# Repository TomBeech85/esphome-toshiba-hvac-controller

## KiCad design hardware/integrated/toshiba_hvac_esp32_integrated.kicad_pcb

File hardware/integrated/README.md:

# Integrated ESP32 Toshiba HVAC Controller

A single-board replacement for the upstream carrier board + ESP32 DevKit stack. The
ESP32-WROOM-32E is soldered directly to the PCB along with everything the DevKit used to
provide, so the board is a fraction of the height — it fits the Haori units that could not
take the socketed DevKit — and is assembled entirely by JLCPCB.

Same outline and JST connector position as the upstream carrier, so the documented
installation fit holds. Firmware is unchanged (`board: esp32dev`, AC UART on GPIO33/32);
the only optional yaml addition is the status LED:

```yaml
status_led:
  pin: GPIO2
```

## What's on it

- **ESP32-WROOM-32E-N8** with EN/IO0 support circuitry, EN + BOOT tact switches (back side)
- **USB-C + CP2102N** with the DevKitC auto-reset circuit — plug in and `esphome run`,
  first flash only, OTA afterwards
- **TXS0108E** level shifter to the indoor unit's 5V UART (identical wiring to upstream)
- **Diode-OR'd power**: the unit's 5V and USB VBUS both feed an AMS1117-3.3 — bench-flash
  on USB and install without touching anything, no backfeed into the AC
- **Status LED** on GPIO2 (front, red)

## Ordering from JLCPCB

1. Upload `production/gerber.zip`. 2 layers, 1.6mm, any colour; leave defaults.
2. Enable **PCB Assembly**, assembled **both sides** (switches and passives are on the back).
3. Upload `production/bom.csv` and `production/positions.csv`.
4. In the part-placement review, check against `render_top.png` / `render_bottom.png`:
   - **U1** antenna pointing at the bare band along the top edge. `positions.csv` already carries
     a +270° correction for it (JLCPCB's library part has a different zero-orientation from the
     KiCad footprint). If the preview shows it 180° out, change `ROT_FIX["U1"]` to `90` in
     `jlc_cpl_fix.py`, re-run it and re-upload.
   - **J2** opening flush with the right-hand edge, pins pointing inboard. No correction applied —
     the build script asserts this orientation, so if the preview disagrees, stop and say so.
   - **J1** pins on the five through-holes, body toward the bottom edge (its CPL entry is shifted
     to the part centroid because the footprint anchor is pad 1).
   - **U4** pin-1 dot against the silkscreen arrow, and on the bottom side **Q1/Q2** leads matching
     their outlines — a 180° error on those two breaks the auto-reset circuit.
5. J1 (the JST S05B-PASK-2) is through-hole: select "economic" assembly with THT if offered,
   or solder it by hand — it is the only through-hole part.

## Verification status

- ERC: clean. DRC: 0 errors, 0 unconnected (KiCad 10, JLCPCB 2-layer rules).
- `build_pcb.py` asserts the USB-C orientation (signal pins inboard of the shell posts, shell
  reaching the board edge). Rev A had this backwards — the opening faced into the board — and the
  error was invisible in the fab layers because KiCad ships no 3D model for this connector.
- `verify_netlist.py` asserts the field-proven J1 pinout (1 TX / 2 GND / 3 +5V / 4 RX),
  shifter channel pairing, UART cross-connects, auto-reset topology and strapping pins;
  `--pcb` additionally diffs every PCB pad net against the schematic.
- Not yet bench-tested. First-article checklist: continuity 5V/3V3/GND, first flash over
  USB-C, OTA update, UART loopback at the JST before connecting to an indoor unit.

## Regenerating

The schematic and board are generated programmatically (KiCad 10):

```
python generate_sch.py                     # schematic from the pin/net map
<KiCad>/bin/python.exe build_pcb.py        # board: placement + routes.py + zones
python verify_netlist.py --pcb             # assertions + schematic/PCB parity
```

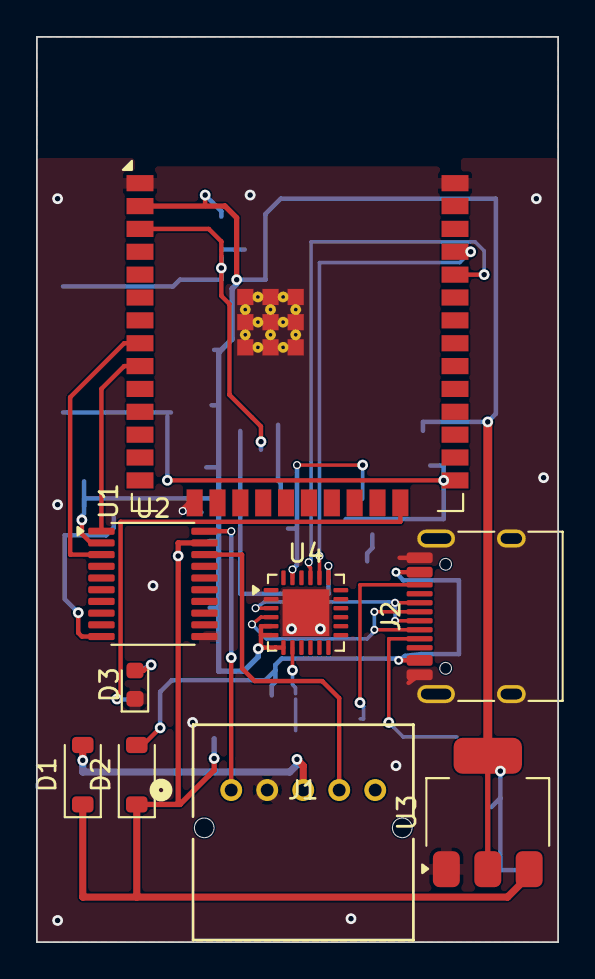
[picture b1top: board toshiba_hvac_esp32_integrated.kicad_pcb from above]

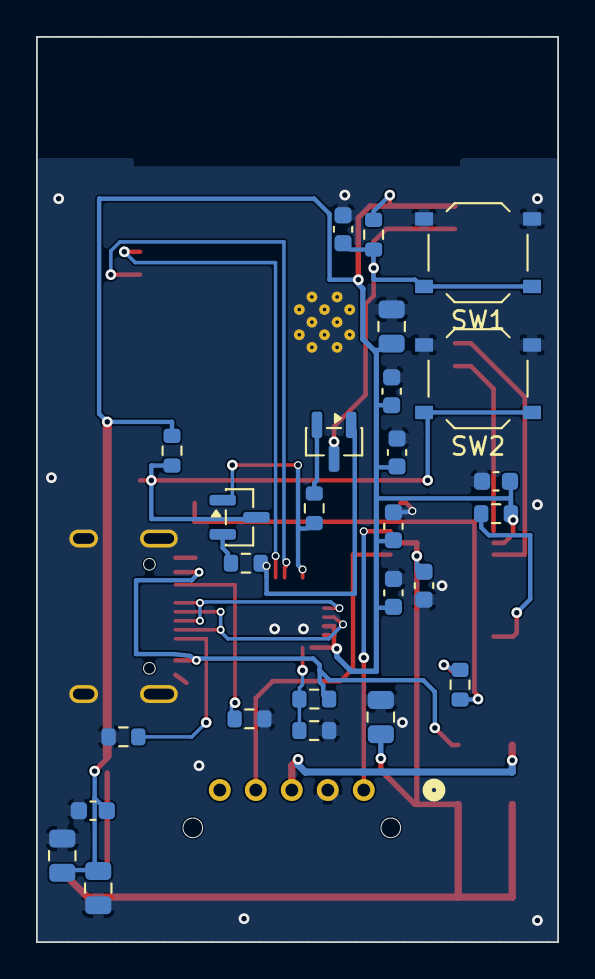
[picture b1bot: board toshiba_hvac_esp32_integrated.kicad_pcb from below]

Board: 2 copper layers, 29.0 x 50.3 mm, 35 parts (26 on the bottom side), 25 nets.

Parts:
C1, C2, C3, C4, C5, C6: 100nF; C_0603_1608Metric
C7, C8: 1uF; C_0603_1608Metric
C9, C10: 10uF; C_0805_2012Metric
C11, C12: 22uF; C_0805_2012Metric
D1, D2: B5819W; D_SOD-123
D3: LED_Red; LED_0603_1608Metric
J1: S05B-PASK-2LFSN; CONN_S05B-PASK-2_JST
J2: TYPE-C-31-M-12; USB_C_Receptacle_HRO_TYPE-C-31-M-12
Q1, Q2: S8050; SOT-23
R1, R2, R3, R4, R5: 10k; R_0603_1608Metric
R6, R7: 5.1k; R_0603_1608Metric
R8: 1k; R_0603_1608Metric
R9: 22k; R_0603_1608Metric
R10: 47k; R_0603_1608Metric
SW1: EN; SW_Push_1P1T_XKB_TS-1187A
SW2: BOOT; SW_Push_1P1T_XKB_TS-1187A
U1: ESP32-WROOM-32E-N8; ESP32-WROOM-32E
U2: TXS0108EPW; TSSOP-20_4.4x6.5mm_P0.65mm
U3: AMS1117-3.3; SOT-223-3_TabPin2
U4: CP2102N-A02-GQFN24; QFN-24-1EP_4x4mm_P0.5mm_EP2.6x2.6mm

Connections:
+3V3: C1.1, C2.1, C4.1, C5.1, C6.1, C8.1, C9.1, C10.1, C12.1, R1.1, R2.1, R3.1, U1.2, U2.2, U3.2, U4.5, U4.6, U4.7
+5V: C3.1, C11.1, D1.1, D2.1, U2.19, U3.3
+5V_AC: D1.2, J1.3
AC_RX: U1.8, U2.3
AC_TX: U1.9, U2.1
CC1: J2.A5, R6.1
CC2: J2.B5, R7.1
DTR: Q2.1, R4.1, U4.23
EN: C7.1, Q1.3, R1.2, SW1.1, U1.3
ESP_RX_5V: J1.4, U2.18
ESP_TX_5V: J1.1, U2.20
GND: C1.2, C2.2, C3.2, C4.2, C5.2, C6.2, C7.2, C8.2, C9.2, C10.2, C11.2, C12.2, D3.1, J1.2, J2.A1, J2.A12, J2.B1, J2.B12, J2.SH, R6.2, R7.2, R10.2, SW1.2, SW2.2, U1.1, U1.15, U1.38, U1.39, U2.11, U3.1, U4.2, U4.25
IO0: Q2.3, R2.2, SW2.1, U1.25
LED_A: D3.2, R8.2
LED_CTRL: R8.1, U1.24
Q1_B: Q1.2, R4.2
Q2_B: Q2.2, R5.2
RTS: Q1.1, R5.1, U4.19
SHIFT_OE: R3.2, U2.10
U0RXD: U1.34, U4.21
U0TXD: U1.35, U4.20
USB_DM: J2.A7, J2.B7, U4.4
USB_DP: J2.A6, J2.B6, U4.3
VBUS: D2.2, J2.A4, J2.A9, J2.B4, J2.B9, R9.1
VBUS_SENSE: R9.2, R10.1, U4.8

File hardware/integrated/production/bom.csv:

Comment,Designator,Footprint,LCSC Part #
ESP32-WROOM-32E-N8,U1,ESP32-WROOM-32E,C701342
TXS0108EPW,U2,TSSOP-20_4.4x6.5mm_P0.65mm,C17206
AMS1117-3.3,U3,SOT-223-3_TabPin2,C6186
CP2102N-A02-GQFN24,U4,QFN-24-1EP_4x4mm_P0.5mm_EP2.6x2.6mm,C969151
S05B-PASK-2LFSN,J1,CONN_S05B-PASK-2_JST,C489718
TYPE-C-31-M-12,J2,USB_C_Receptacle_HRO_TYPE-C-31-M-12,C165948
B5819W,"D1, D2",D_SOD-123,C8598
LED_Red_KT-0603R,D3,LED_0603_1608Metric,C2286
S8050,"Q1, Q2",SOT-23,C2146
TS-1187A-B-A-B,"SW1, SW2",SW_SPST_XKB_TS-1187A-B-A-B,C318884
10k,"R1, R2, R3, R4, R5",R_0603_1608Metric,C25804
5.1k,"R6, R7",R_0603_1608Metric,C23186
1k,R8,R_0603_1608Metric,C21190
22k,R9,R_0603_1608Metric,C31850
47k,R10,R_0603_1608Metric,C25819
100nF,"C1, C2, C3, C4, C5, C6",C_0603_1608Metric,C14663
1uF,"C7, C8",C_0603_1608Metric,C15849
10uF,"C9, C10",C_0805_2012Metric,C15850
22uF,"C11, C12",C_0805_2012Metric,C45783
